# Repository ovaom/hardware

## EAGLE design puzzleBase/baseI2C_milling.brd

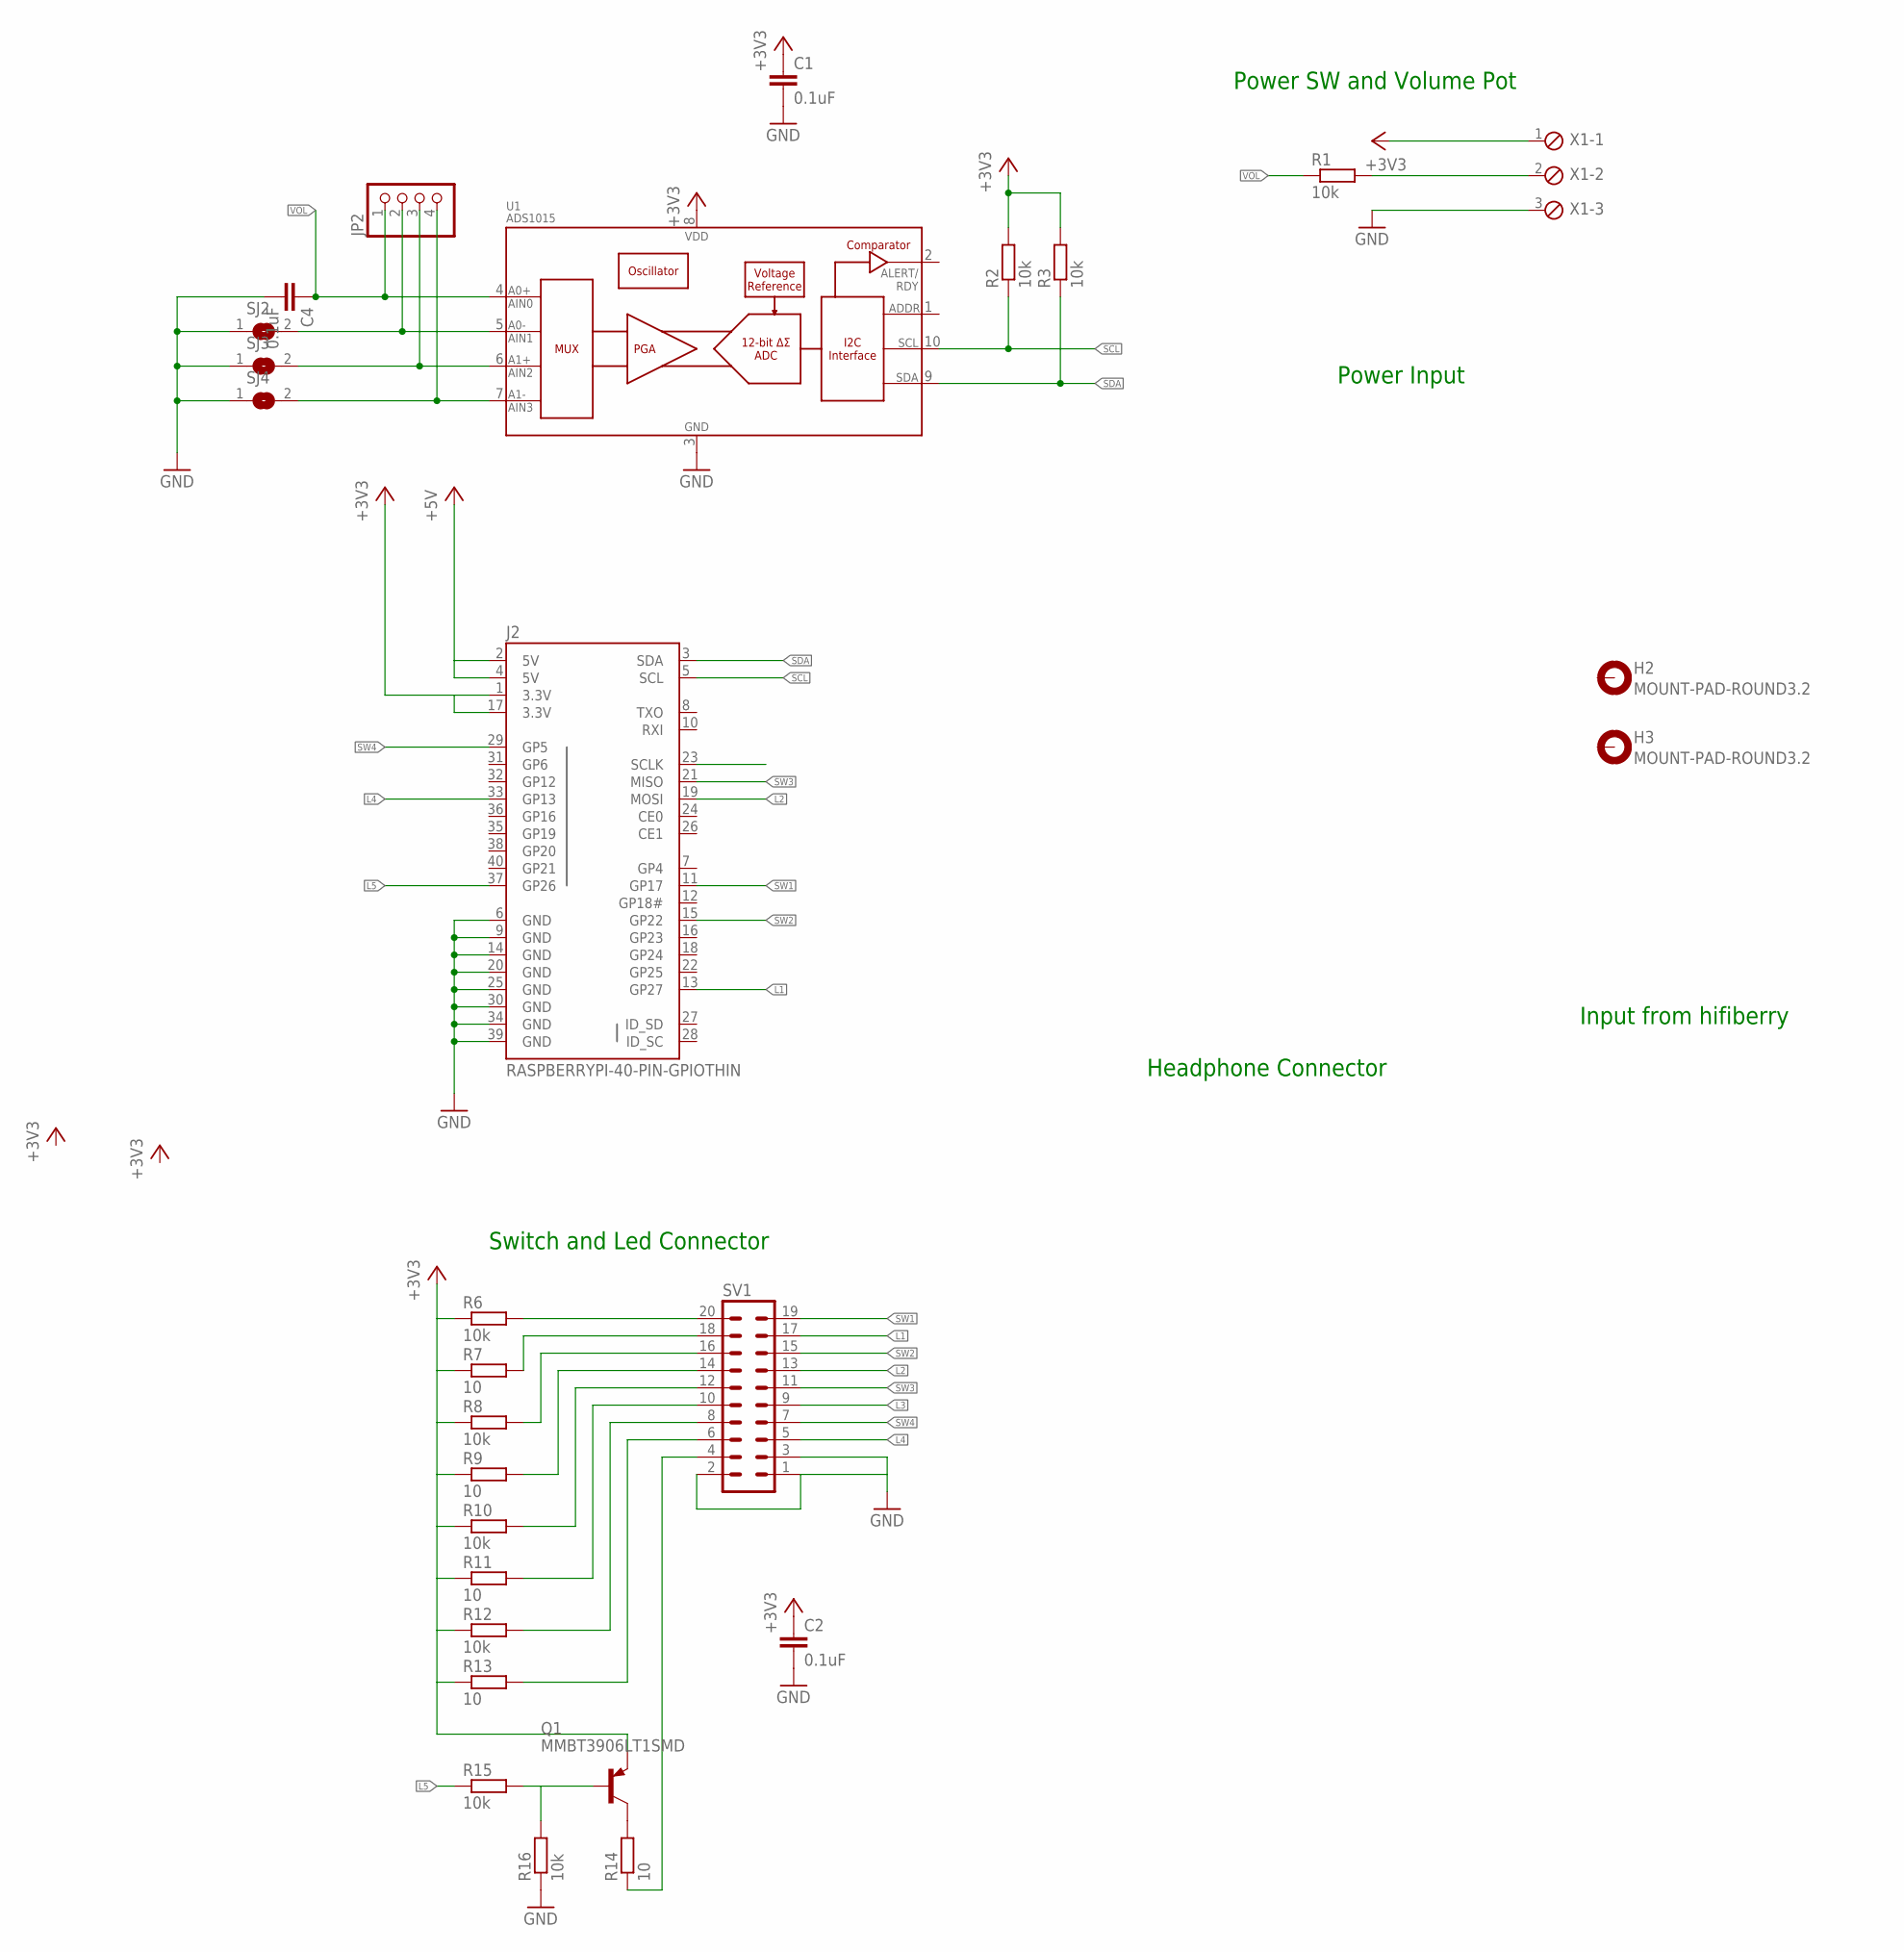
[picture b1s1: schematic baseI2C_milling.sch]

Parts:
C1, C2, C4: 0.1uF; C0805
H2, H3: MOUNT-PAD-ROUND3.2; 3,2-PAD
J2: RASPBERRYPI-40-PIN-GPIOTHIN; 2X20-SHROUDED-THIN
JP2: PINHD-1X4; 1X04
Q1: MMBT3906LT1SMD; SOT23-BEC
R1, R2, R3, R6, R8, R10, R12, R15, R16: 10k; R0805
R7, R9, R11, R13, R14: 10; R0805
SJ2, SJ3, SJ4: SOLDERJUMPER; SOLDERJUMPER_ARROW_NOPASTE
SV1: ML20
U1: ADS1015; MSOP10
X1: MPT3; 3POL254

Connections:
+3V3: C1.1, C2.1, J2.1 (3.3V), J2.17 (3.3V), Q1.E, R2.2, R3.2, R6.1, R7.1, R8.1, R9.1, R10.1, R11.1, R12.1, R13.1, U1.8 (VDD), X1.1
+5V: J2.2 (5V), J2.4 (5V)
GND: C1.2, C2.2, C4.2, J2.6 (GND), J2.9 (GND), J2.14 (GND), J2.20 (GND), J2.25 (GND), J2.30 (GND), J2.34 (GND), J2.39 (GND), R16.1, SJ2.1, SJ3.1, SJ4.1, SV1.1, SV1.2, SV1.3, U1.3 (VSS), X1.3
L1: J2.13 (GP27), SV1.17
L2: J2.19 (MOSI), SV1.13
L3: J2.23 (SCLK), SV1.9
L4: J2.33 (GP13), SV1.5
L5: J2.37 (GP26), R15.1
unnamed: Q1.C, R14.2
unnamed: Q1.B, R15.2, R16.2
unnamed: R8.2, SV1.16
unnamed: R9.2, SV1.14
unnamed: R6.2, SV1.20
unnamed: R7.2, SV1.18
unnamed: R10.2, SV1.12
unnamed: JP2.2, SJ2.2, U1.5 (AIN1)
unnamed: R1.2, X1.2
unnamed: R11.2, SV1.10
unnamed: JP2.3, SJ3.2, U1.6 (AIN2)
unnamed: JP2.4, SJ4.2, U1.7 (AIN3)
unnamed: R12.2, SV1.8
unnamed: R13.2, SV1.6
unnamed: R14.1, SV1.4
SCL: J2.5 (SCL), R2.1, U1.10 (SCL)
SDA: J2.3 (SDA), R3.1, U1.9 (SDA)
SW1: J2.11 (GP17), SV1.19
SW2: J2.15 (GP22), SV1.15
SW3: J2.21 (MISO), SV1.11
SW4: J2.29 (GP5), SV1.7
VOL: C4.1, JP2.1, R1.1, U1.4 (AIN0)

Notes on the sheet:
Input from hifiberry
Headphone Connector
Power Input
Switch and Led Connector
Power SW and Volume Pot

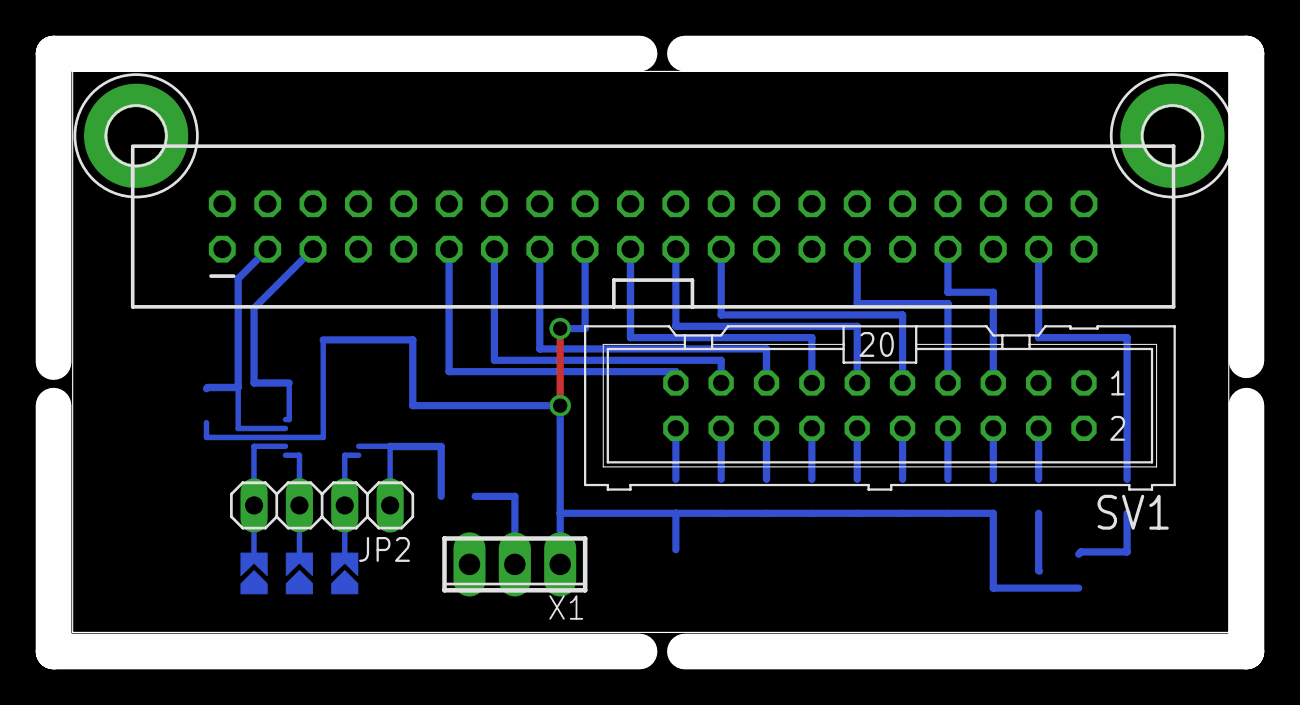
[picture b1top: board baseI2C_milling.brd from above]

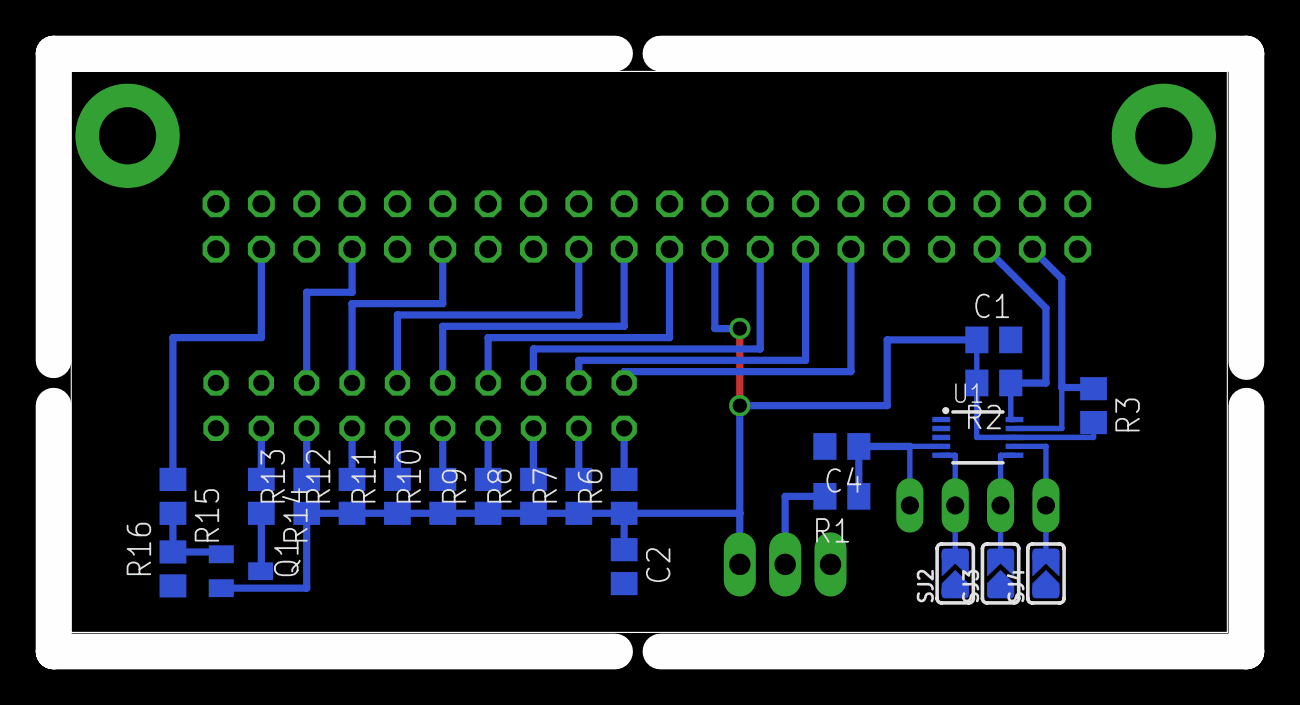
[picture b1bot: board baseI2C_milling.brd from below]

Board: 2 copper layers, 66.8 x 33.5 mm, 28 parts (22 on the bottom side), 30 nets.

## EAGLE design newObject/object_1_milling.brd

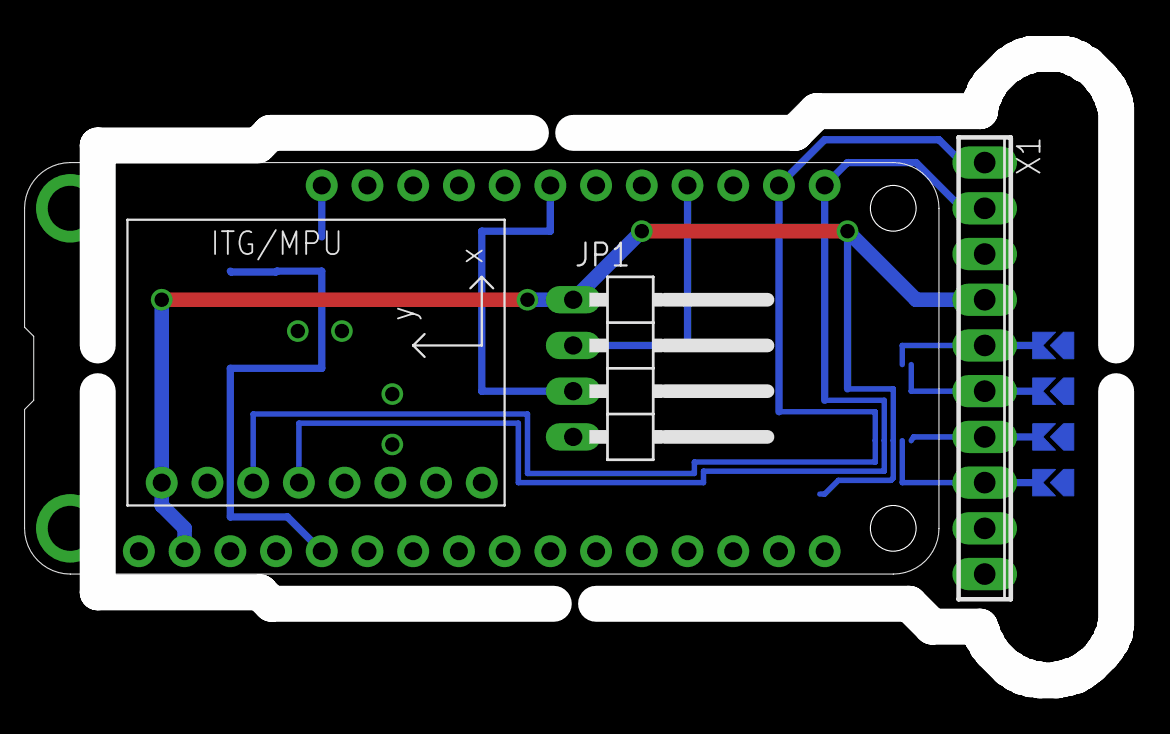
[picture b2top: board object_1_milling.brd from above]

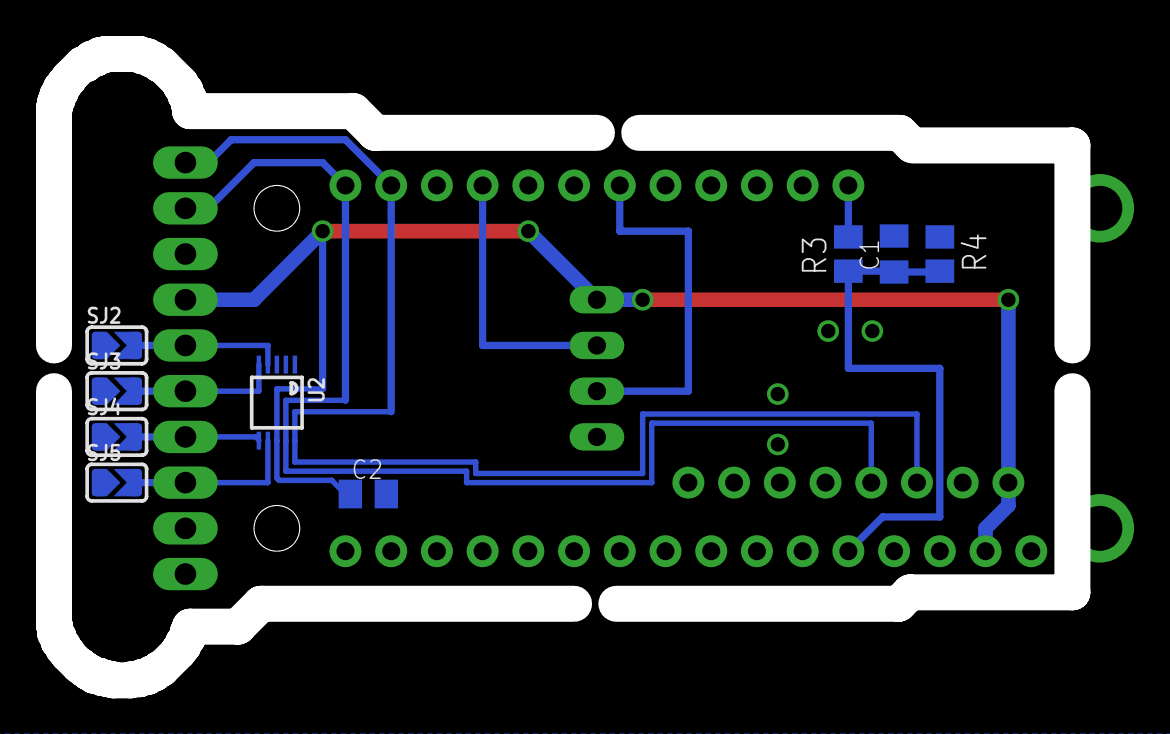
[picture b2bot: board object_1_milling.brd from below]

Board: 2 copper layers, 56.6 x 34.8 mm, 13 parts (9 on the bottom side), 12 nets.

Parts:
C1: C0805K
C2: .1; C0805K
JP1: 1X04/90
MS1: FEATHERWING_NODIM; FEATHERWING_DIM
R3: 1M; M0805
R4: 220k; M0805
SJ2, SJ3, SJ4, SJ5: SOLDERJUMPER_ARROW_NOPASTE
U1: GY-521MPU6050; GY-521
U2: MSOP10
X1: 10POL254

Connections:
+3V3: C2.1, JP1.1, MS1.2, U1.VCC, U2.8, X1.4
AD0: C1.1, MS1.5, R3.1, R4.2
BTN: JP1.3, MS1.23
GND: C1.2, C2.2, JP1.4, MS1.4, R4.1, SJ2.1, SJ3.1, SJ4.1, SJ5.1, U1.GND, U2.1, U2.3, X1.3, X1.9, X1.10
LED_GND: JP1.2, MS1.20
unnamed: SJ2.2, U2.4, X1.5
unnamed: SJ3.2, U2.5, X1.6
unnamed: SJ4.2, U2.6, X1.7
unnamed: SJ5.2, U2.7, X1.8
SCL: MS1.18, U1.SCL, U2.10, X1.1
SDA: MS1.17, U1.SDA, U2.9, X1.2
VBAT: MS1.28, R3.2

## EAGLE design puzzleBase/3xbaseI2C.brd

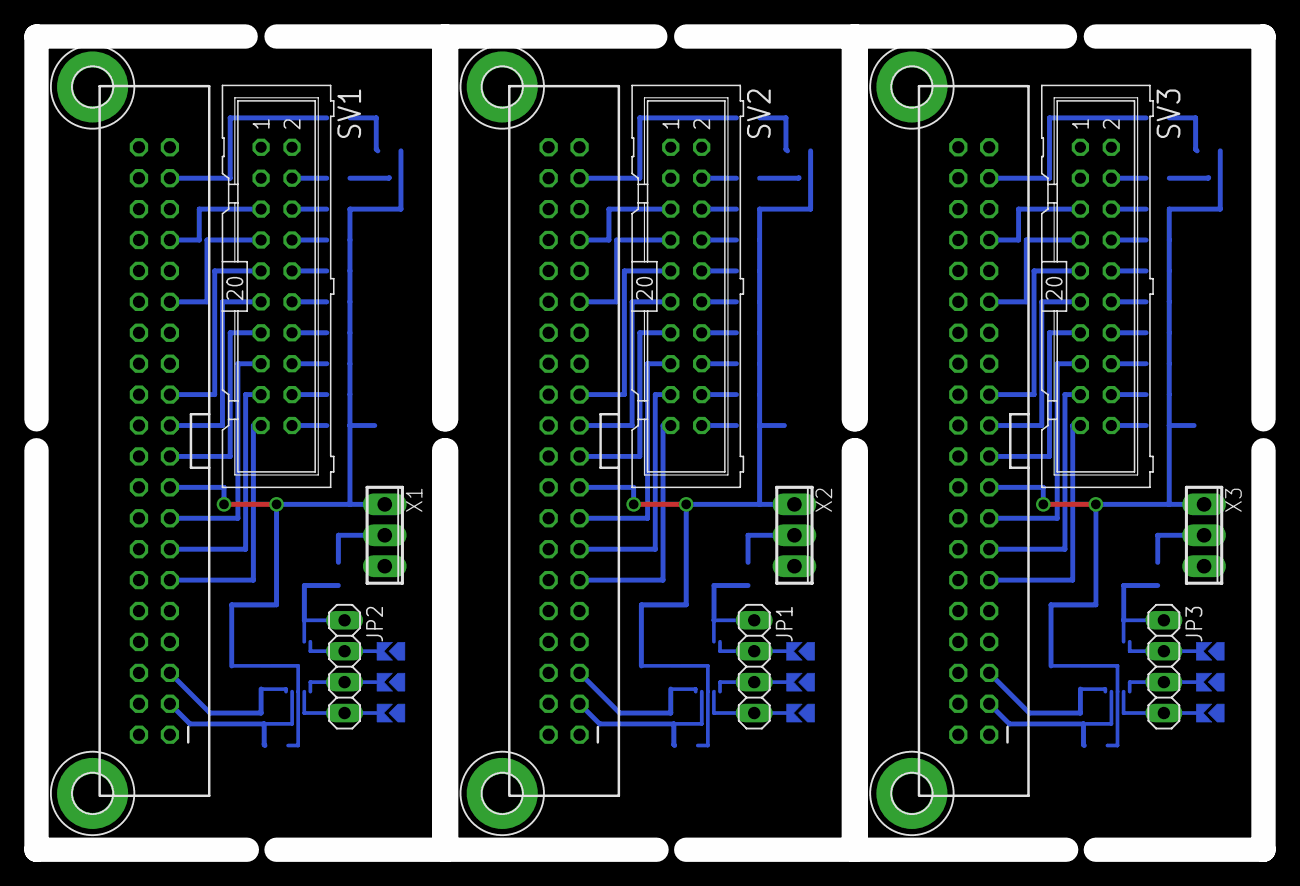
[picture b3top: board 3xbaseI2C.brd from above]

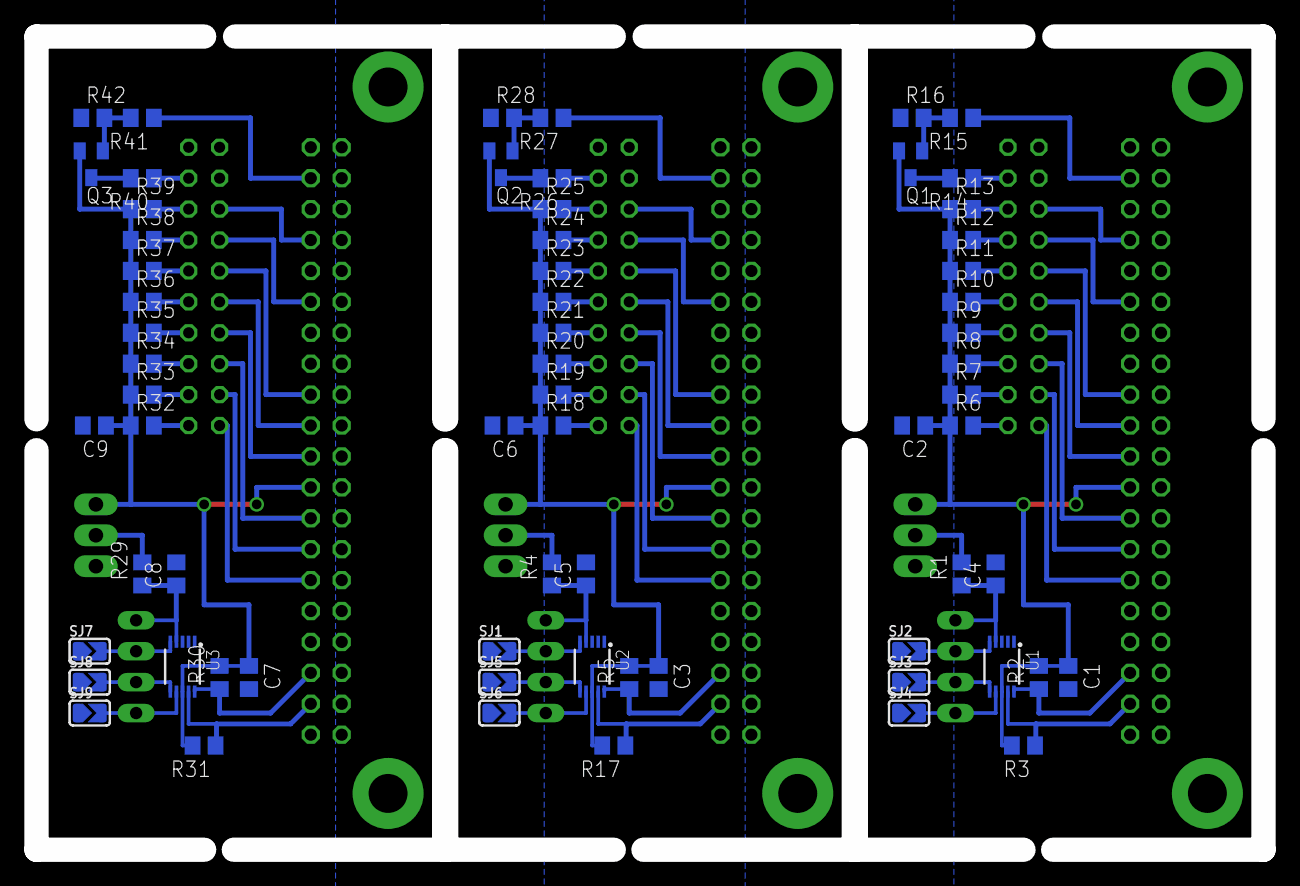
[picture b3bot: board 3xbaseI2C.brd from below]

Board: 2 copper layers, 100.8 x 66.8 mm, 84 parts (66 on the bottom side), 90 nets.

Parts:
C1, C2, C3, C4, C5, C6, C7, C8, C9: 0.1uF; C0805
H1, H2, H3, H4, H5, H6: MOUNT-PAD-ROUND3.2; 3,2-PAD
J1, J2, J3: RASPBERRYPI-40-PIN-GPIOTHIN; 2X20-SHROUDED-THIN
JP1, JP2, JP3: 1X04
Q1, Q2, Q3: MMBT3906LT1SMD; SOT23-BEC
R1, R2, R3, R4, R5, R6, R8, R10, R12, R15, R16, R17, R18, R20, R22, R24, R27, R28, R29, R30, R31, R32, R34, R36, R38, R41, R42: 10k; R0805
R7, R9, R11, R13, R14, R19, R21, R23, R25, R26, R33, R35, R37, R39, R40: 10; R0805
SJ1, SJ2, SJ3, SJ4, SJ5, SJ6, SJ7, SJ8, SJ9: SOLDERJUMPER_ARROW_NOPASTE
SV1, SV2, SV3: ML20
U1, U2, U3: ADS1015; MSOP10
X1, X2, X3: 3POL254

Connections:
+3V1: C3.1, C6.1, J1.1, J1.17, Q2.E, R5.2, R17.2, R18.1, R19.1, R20.1, R21.1, R22.1, R23.1, R24.1, R25.1, U2.8, X2.1
+3V2: C7.1, C9.1, J3.1, J3.17, Q3.E, R30.2, R31.2, R32.1, R33.1, R34.1, R35.1, R36.1, R37.1, R38.1, R39.1, U3.8, X3.1
+3V3: C1.1, C2.1, J2.1, J2.17, Q1.E, R2.2, R3.2, R6.1, R7.1, R8.1, R9.1, R10.1, R11.1, R12.1, R13.1, U1.8, X1.1
+5V: J2.2, J2.4
+5V1: J1.2, J1.4
+5V2: J3.2, J3.4
GND: C1.2, C2.2, C4.2, J2.6, J2.9, J2.14, J2.20, J2.25, J2.30, J2.34, J2.39, R16.1, SJ2.1, SJ3.1, SJ4.1, SV1.1, SV1.2, SV1.3, U1.3, X1.3
GND1: C3.2, C5.2, C6.2, J1.6, J1.9, J1.14, J1.20, J1.25, J1.30, J1.34, J1.39, R28.1, SJ1.1, SJ5.1, SJ6.1, SV2.1, SV2.2, SV2.3, U2.3, X2.3
GND2: C7.2, C8.2, C9.2, J3.6, J3.9, J3.14, J3.20, J3.25, J3.30, J3.34, J3.39, R42.1, SJ7.1, SJ8.1, SJ9.1, SV3.1, SV3.2, SV3.3, U3.3, X3.3
L1: J2.13, SV1.17
L2: J2.19, SV1.13
L3: J2.23, SV1.9
L4: J2.33, SV1.5
L5: J2.37, R15.1
L6: J1.13, SV2.17
L7: J1.19, SV2.13
L8: J1.23, SV2.9
L9: J1.33, SV2.5
L10: J1.37, R27.1
L11: J3.13, SV3.17
L12: J3.19, SV3.13
L13: J3.23, SV3.9
L14: J3.33, SV3.5
L15: J3.37, R41.1
unnamed: Q1.C, R14.2
unnamed: Q1.B, R15.2, R16.2
unnamed: R8.2, SV1.16
unnamed: R9.2, SV1.14
unnamed: R6.2, SV1.20
unnamed: R7.2, SV1.18
unnamed: R10.2, SV1.12
unnamed: JP2.2, SJ2.2, U1.5
unnamed: R1.2, X1.2
unnamed: R11.2, SV1.10
unnamed: JP2.3, SJ3.2, U1.6
unnamed: JP2.4, SJ4.2, U1.7
unnamed: R12.2, SV1.8
unnamed: R13.2, SV1.6
unnamed: R14.1, SV1.4
unnamed: R4.2, X2.2
unnamed: JP1.2, SJ1.2, U2.5
unnamed: JP1.3, SJ5.2, U2.6
unnamed: JP1.4, SJ6.2, U2.7
unnamed: R18.2, SV2.20
unnamed: R19.2, SV2.18
unnamed: Q2.C, R26.2
unnamed: Q2.B, R27.2, R28.2
unnamed: R20.2, SV2.16
unnamed: R21.2, SV2.14
unnamed: R22.2, SV2.12
unnamed: R23.2, SV2.10
unnamed: R24.2, SV2.8
unnamed: R25.2, SV2.6
unnamed: R26.1, SV2.4
unnamed: R29.2, X3.2
unnamed: JP3.2, SJ7.2, U3.5
unnamed: JP3.3, SJ8.2, U3.6
unnamed: JP3.4, SJ9.2, U3.7
unnamed: R32.2, SV3.20
unnamed: R33.2, SV3.18
unnamed: Q3.C, R40.2
unnamed: Q3.B, R41.2, R42.2
unnamed: R34.2, SV3.16
unnamed: R35.2, SV3.14
unnamed: R36.2, SV3.12
unnamed: R37.2, SV3.10
unnamed: R38.2, SV3.8
unnamed: R39.2, SV3.6
unnamed: R40.1, SV3.4
SCL: J2.5, R2.1, U1.10
SCL1: J1.5, R5.1, U2.10
SCL2: J3.5, R30.1, U3.10
SDA: J2.3, R3.1, U1.9
SDA1: J1.3, R17.1, U2.9
SDA2: J3.3, R31.1, U3.9
SW1: J2.11, SV1.19
SW2: J2.15, SV1.15
SW3: J2.21, SV1.11
SW4: J2.29, SV1.7
SW5: J1.11, SV2.19
SW6: J1.15, SV2.15
SW7: J1.21, SV2.11
SW8: J1.29, SV2.7
SW9: J3.11, SV3.19
SW10: J3.15, SV3.15
SW11: J3.21, SV3.11
SW12: J3.29, SV3.7
VOL: C4.1, JP2.1, R1.1, U1.4
VOL1: C5.1, JP1.1, R4.1, U2.4
VOL2: C8.1, JP3.1, R29.1, U3.4

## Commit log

2019-01-23 Commit with all files produced for the RPi shield and the objects
2019-01-29 Cleanup Ghostfiles and name everything correctly
2019-01-29 Cleanup RPi hat files

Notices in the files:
parts and their libraries:
SparkFun-Boards: Licensing: Creative Commons ShareAlike 4.0 International - https://creativecommons.org/licenses/by-sa/4.0
microbuilder: This work is placed in the public domain, and may be freely used for commercial and non-commercial work with the following conditions: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
